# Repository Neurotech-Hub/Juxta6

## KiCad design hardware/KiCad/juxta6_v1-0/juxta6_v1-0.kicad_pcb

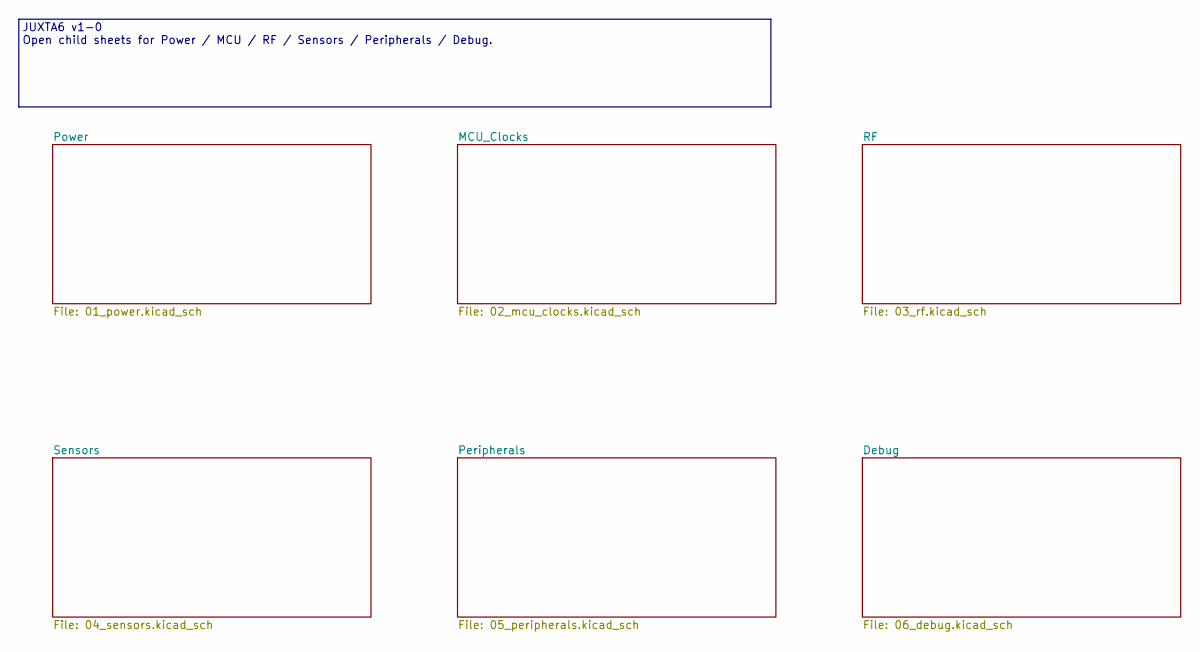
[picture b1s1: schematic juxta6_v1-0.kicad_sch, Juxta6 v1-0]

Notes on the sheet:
JUXTA6 v1-0 Open child sheets for Power / MCU / RF / Sensors / Peripherals / Debug.

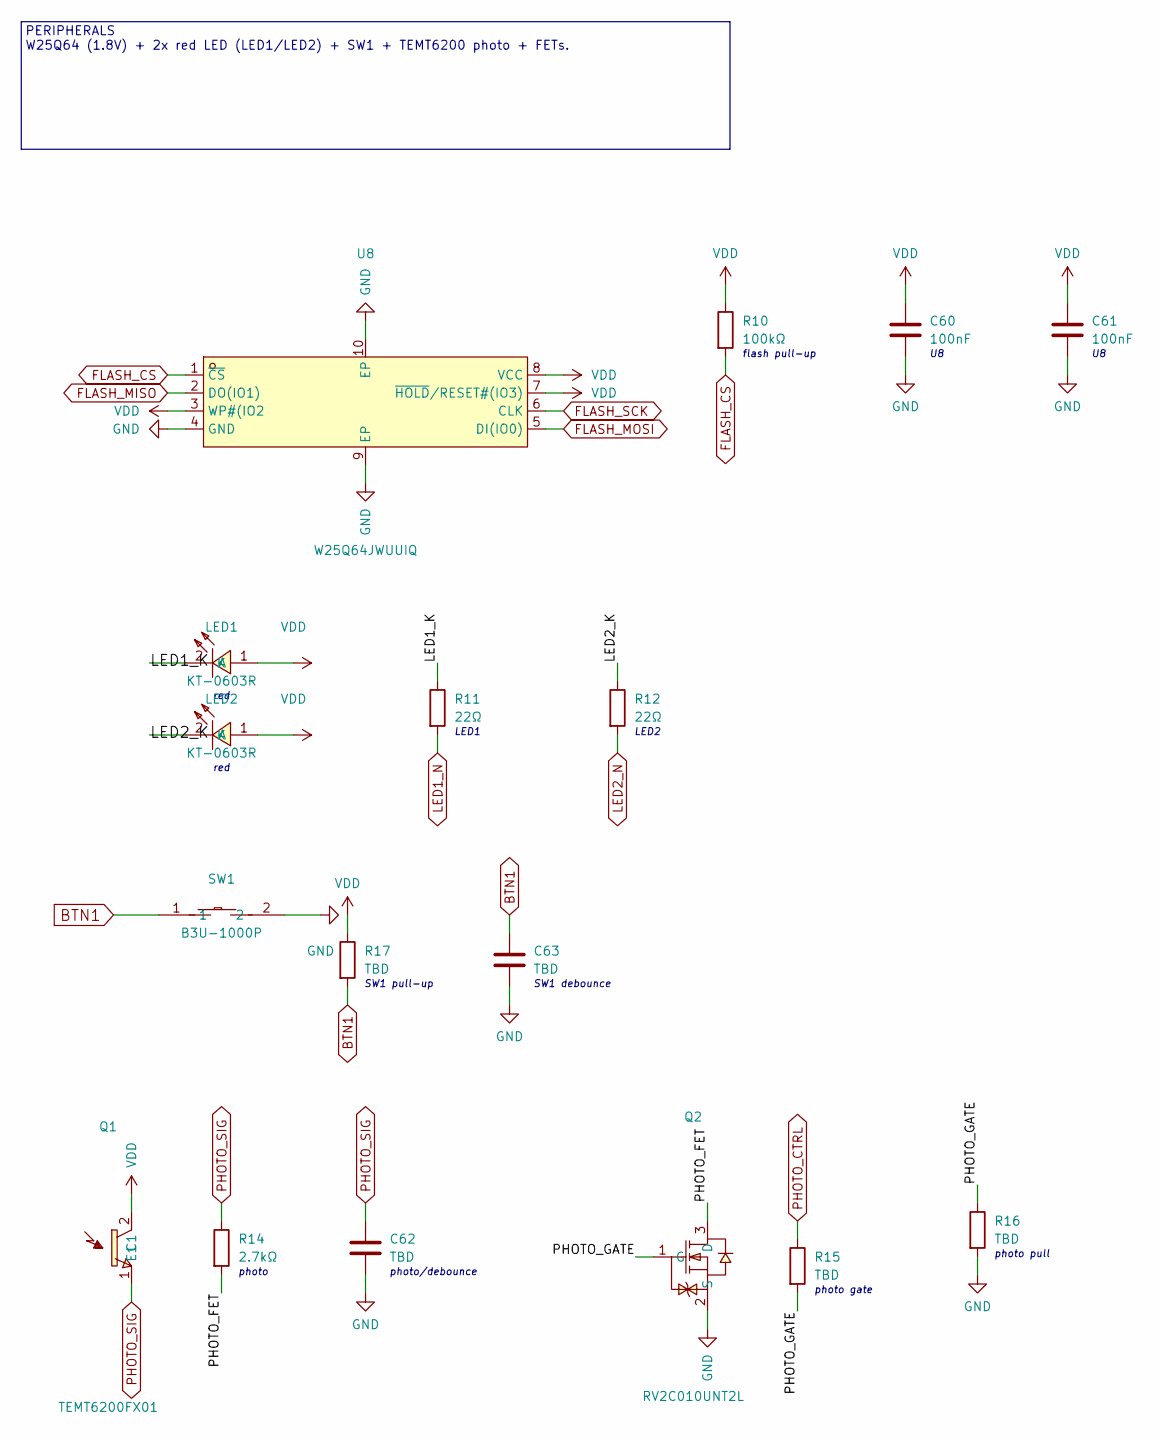
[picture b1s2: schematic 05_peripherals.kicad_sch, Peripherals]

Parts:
C60, C61: 100nF; C_0201_0603Metric
C62, C63: TBD; C_0201_0603Metric
LED1, LED2: KT-0603R; LED-SMD_L1.6-W0.8-R-RD; LCSC C2286
Q1: TEMT6200FX01; SENSORS-SMD_0805; LCSC C143695
Q2: RV2C010UNT2L; X2-DFN1006-3_L1.0-W0.6-BR; LCSC C570828
R10: 100kΩ; R_0201_0603Metric
R11, R12: 22Ω; R_0201_0603Metric
R14: 2.7kΩ; R_0201_0603Metric
R15, R16, R17: TBD; R_0201_0603Metric
SW1: B3U-1000P; KEY-SMD_B3U-1000PM; LCSC C231329
U8: W25Q64JWUUIQ; USON-8_L4.0-W3.0-P0.80-BL_WINBOND_UU; LCSC C6604692

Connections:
/Peripherals/LED1_K: LED1.2 (K), R11.1
/Peripherals/LED2_K: LED2.2 (K), R12.1
/Peripherals/PHOTO_FET: Q2.3 (D), R14.2
/Peripherals/PHOTO_GATE: Q2.1 (G), R15.2, R16.1
BTN1: C63.1, R17.2, SW1.1; also elsewhere on the board
FLASH_CS: R10.2, U8.1 (~CS); also elsewhere on the board
FLASH_MISO: U8.2 (DO(IO1)); also elsewhere on the board
FLASH_MOSI: U8.5 (DI(IO0)); also elsewhere on the board
FLASH_SCK: U8.6 (CLK); also elsewhere on the board
GND: C60.2, C61.2, C62.2, C63.2, Q2.2 (S), R16.2, SW1.2, U8.4 (GND), U8.9 (EP), U8.10 (EP); also elsewhere on the board
LED1_N: R11.2; also elsewhere on the board
LED2_N: R12.2; also elsewhere on the board
PHOTO_CTRL: R15.1; also elsewhere on the board
PHOTO_SIG: C62.1, Q1.1 (E1), R14.1; also elsewhere on the board
VDD: C60.1, C61.1, LED1.1 (A), LED2.1 (A), Q1.2 (C1), R10.1, R17.1, U8.3 (WP#(IO2), U8.7 (~HOLD/RESET#(IO3)), U8.8 (VCC); also elsewhere on the board

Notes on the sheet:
red
LED2
photo gate
photo
flash pull-up
SW1 debounce
LED1
photo pull
SW1 pull-up
photo/debounce
PERIPHERALS W25Q64 (1.8V) + 2x red LED (LED1/LED2) + SW1 + TEMT6200 photo + FETs.

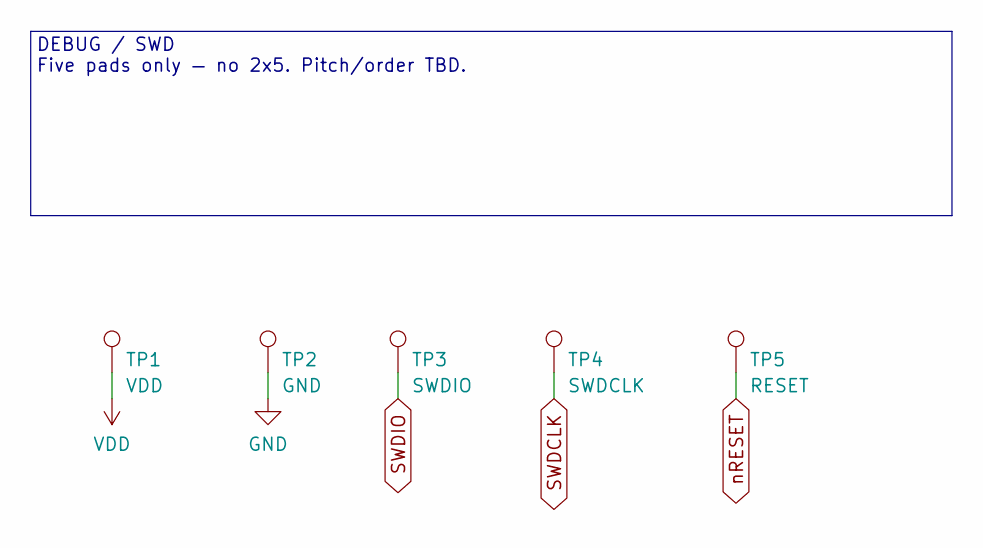
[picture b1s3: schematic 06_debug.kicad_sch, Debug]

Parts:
TP1: VDD; TestPoint_Pad_D1.5mm
TP2: GND; TestPoint_Pad_D1.5mm
TP3: SWDIO; TestPoint_Pad_D1.5mm
TP4: SWDCLK; TestPoint_Pad_D1.5mm
TP5: RESET; TestPoint_Pad_D1.5mm

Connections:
GND: TP2.1 (1_1); also elsewhere on the board
SWDCLK: TP4.1 (1_1); also elsewhere on the board
SWDIO: TP3.1 (1_1); also elsewhere on the board
VDD: TP1.1 (1_1); also elsewhere on the board
nRESET: TP5.1 (1_1); also elsewhere on the board

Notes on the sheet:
DEBUG / SWD Five pads only — no 2x5. Pitch/order TBD.

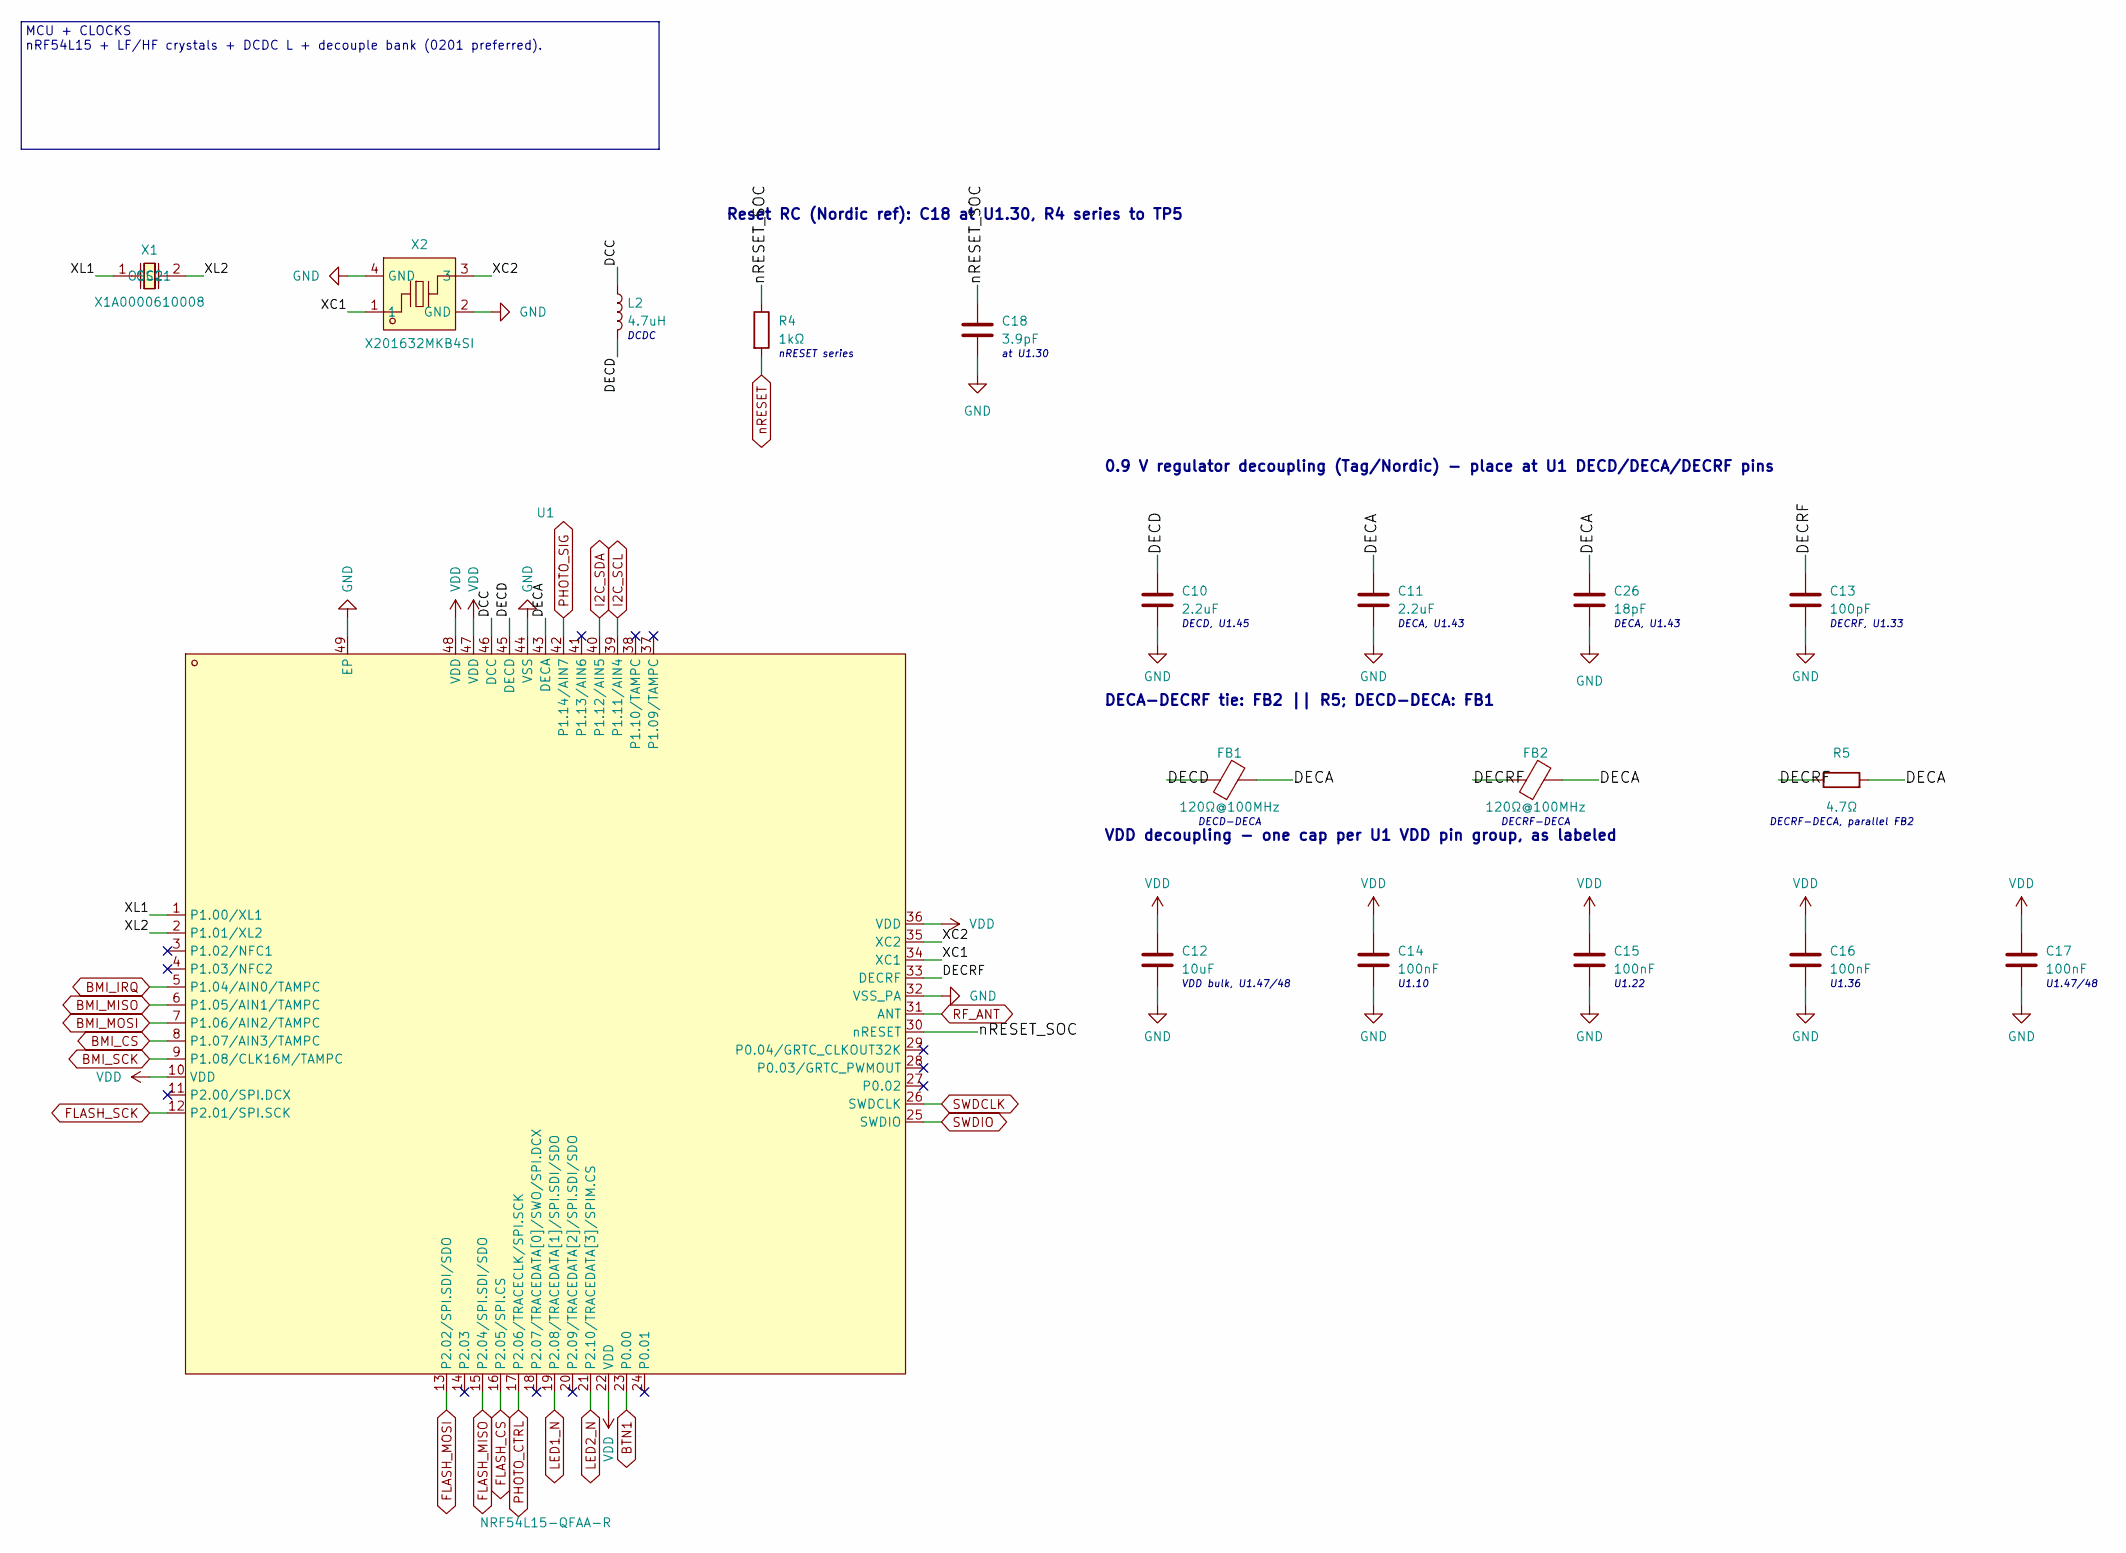
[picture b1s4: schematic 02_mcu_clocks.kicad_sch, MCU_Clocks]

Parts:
C10, C11: 2.2uF; C_0201_0603Metric
C12: 10uF; C_0201_0603Metric
C13: 100pF; C_0201_0603Metric
C14, C15, C16, C17: 100nF; C_0201_0603Metric
C18: 3.9pF; C_0201_0603Metric
C26: 18pF; C_0201_0603Metric
FB1, FB2: 120Ω@100MHz; L_0201_0603Metric
L2: 4.7uH; L_0603_1608Metric
R4: 1kΩ; R_0201_0603Metric
R5: 4.7Ω; R_0201_0603Metric
U1: NRF54L15-QFAA-R; QFN-48_L6.0-W6.0-P0.40-TL-EP4.6; LCSC C42458750
X1: X1A0000610008; OSC-SMD_L2.0-W1.2; LCSC C96341
X2: X201632MKB4SI; CRYSTAL-SMD_4P-L2.0-W1.6-BL; LCSC C718072

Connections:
/MCU_Clocks/DCC: L2.1, U1.46 (DCC)
/MCU_Clocks/DECA: C11.1, C26.1, FB1.2, FB2.2, R5.2, U1.43 (DECA)
/MCU_Clocks/DECD: C10.1, FB1.1, L2.2, U1.45 (DECD)
/MCU_Clocks/DECRF: C13.1, FB2.1, R5.1, U1.33 (DECRF)
/MCU_Clocks/XC1: U1.34 (XC1), X2.1
/MCU_Clocks/XC2: U1.35 (XC2), X2.3
/MCU_Clocks/XL1: U1.1 (P1.00/XL1), X1.1 (OSC1)
/MCU_Clocks/XL2: U1.2 (P1.01/XL2), X1.2 (OSC2)
/MCU_Clocks/nRESET_SOC: C18.1, R4.1, U1.30 (nRESET)
BMI_CS: U1.8 (P1.07/AIN3/TAMPC); also elsewhere on the board
BMI_IRQ: U1.5 (P1.04/AIN0/TAMPC); also elsewhere on the board
BMI_MISO: U1.6 (P1.05/AIN1/TAMPC); also elsewhere on the board
BMI_MOSI: U1.7 (P1.06/AIN2/TAMPC); also elsewhere on the board
BMI_SCK: U1.9 (P1.08/CLK16M/TAMPC); also elsewhere on the board
BTN1: U1.23 (P0.00); also elsewhere on the board
FLASH_CS: U1.16 (P2.05/SPI.CS); also elsewhere on the board
FLASH_MISO: U1.15 (P2.04/SPI.SDI/SDO); also elsewhere on the board
FLASH_MOSI: U1.13 (P2.02/SPI.SDI/SDO); also elsewhere on the board
FLASH_SCK: U1.12 (P2.01/SPI.SCK); also elsewhere on the board
GND: C10.2, C11.2, C12.2, C13.2, C14.2, C15.2, C16.2, C17.2, C18.2, C26.2, U1.32 (VSS_PA), U1.44 (VSS), U1.49 (EP), X2.2 (GND), X2.4 (GND); also elsewhere on the board
I2C_SCL: U1.39 (P1.11/AIN4); also elsewhere on the board
I2C_SDA: U1.40 (P1.12/AIN5); also elsewhere on the board
LED1_N: U1.19 (P2.08/TRACEDATA[1]/SPI.SDI/SDO); also elsewhere on the board
LED2_N: U1.21 (P2.10/TRACEDATA[3]/SPIM.CS); also elsewhere on the board
PHOTO_CTRL: U1.17 (P2.06/TRACECLK/SPI.SCK); also elsewhere on the board
PHOTO_SIG: U1.42 (P1.14/AIN7); also elsewhere on the board
RF_ANT: U1.31 (ANT); also elsewhere on the board
SWDCLK: U1.26 (SWDCLK); also elsewhere on the board
SWDIO: U1.25 (SWDIO); also elsewhere on the board
VDD: C12.1, C14.1, C15.1, C16.1, C17.1, U1.10 (VDD), U1.22 (VDD), U1.36 (VDD), U1.47 (VDD), U1.48 (VDD); also elsewhere on the board
nRESET: R4.2; also elsewhere on the board

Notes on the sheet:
U1.10
DCDC
DECA, U1.43
DECD, U1.45
0.9 V regulator decoupling (Tag/Nordic) - place at U1 DECD/DECA/DECRF pins
VDD bulk, U1.47/48
VDD decoupling - one cap per U1 VDD pin group, as labeled
nRESET series
at U1.30
DECRF, U1.33
U1.47/48
U1.22
Reset RC (Nordic ref): C18 at U1.30, R4 series to TP5
DECD-DECA
DECRF-DECA, parallel FB2
U1.36
DECRF-DECA
DECA-DECRF tie: FB2 || R5; DECD-DECA: FB1
MCU + CLOCKS nRF54L15 + LF/HF crystals + DCDC L + decouple bank (0201 preferred).

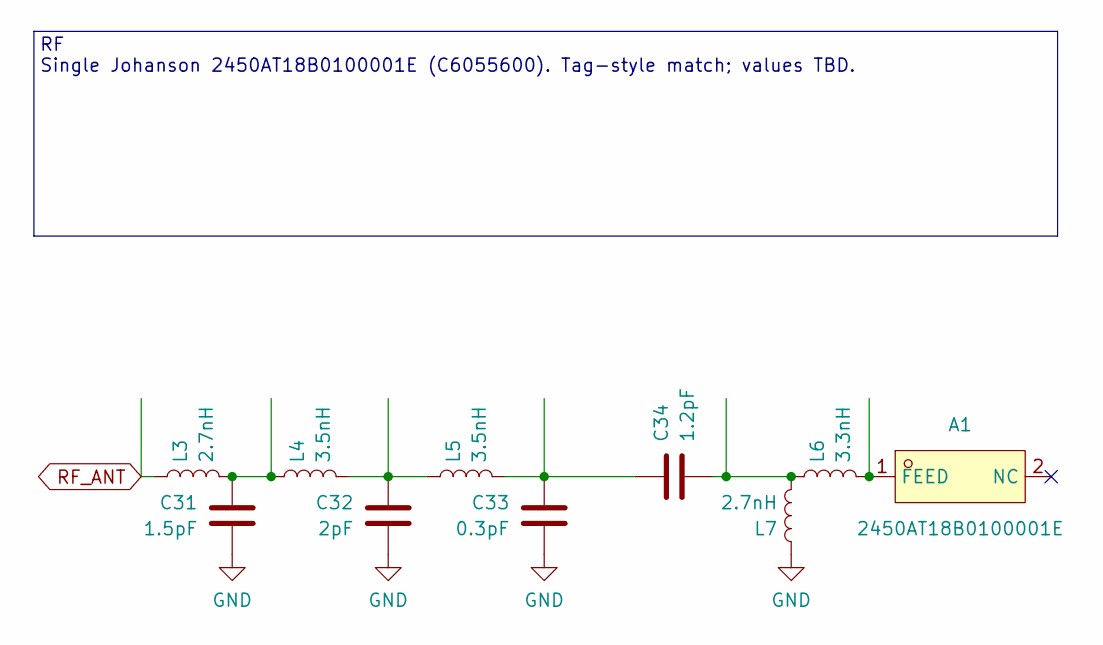
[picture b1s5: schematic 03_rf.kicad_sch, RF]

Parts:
A1: 2450AT18B0100001E; ANT-SMD_L3.2-W1.6
C31: 1.5pF; C_0201_0603Metric
C32: 2pF; C_0201_0603Metric
C33: 0.3pF; C_0201_0603Metric
C34: 1.2pF; C_0201_0603Metric
L3, L7: 2.7nH; L_0201_0603Metric
L4, L5: 3.5nH; L_0201_0603Metric
L6: 3.3nH; L_0201_0603Metric

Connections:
GND: C31.2, C32.2, C33.2, L7.1; also elsewhere on the board
unnamed: A1.1 (FEED_1), L6.2
unnamed: C31.1, L3.2, L4.1
unnamed: C32.1, L4.2, L5.1
unnamed: C33.1, C34.1, L5.2
unnamed: C34.2, L6.1, L7.2
RF_ANT: L3.1; also elsewhere on the board

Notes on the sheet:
RF Single Johanson 2450AT18B0100001E (C6055600). Tag-style match; values TBD.

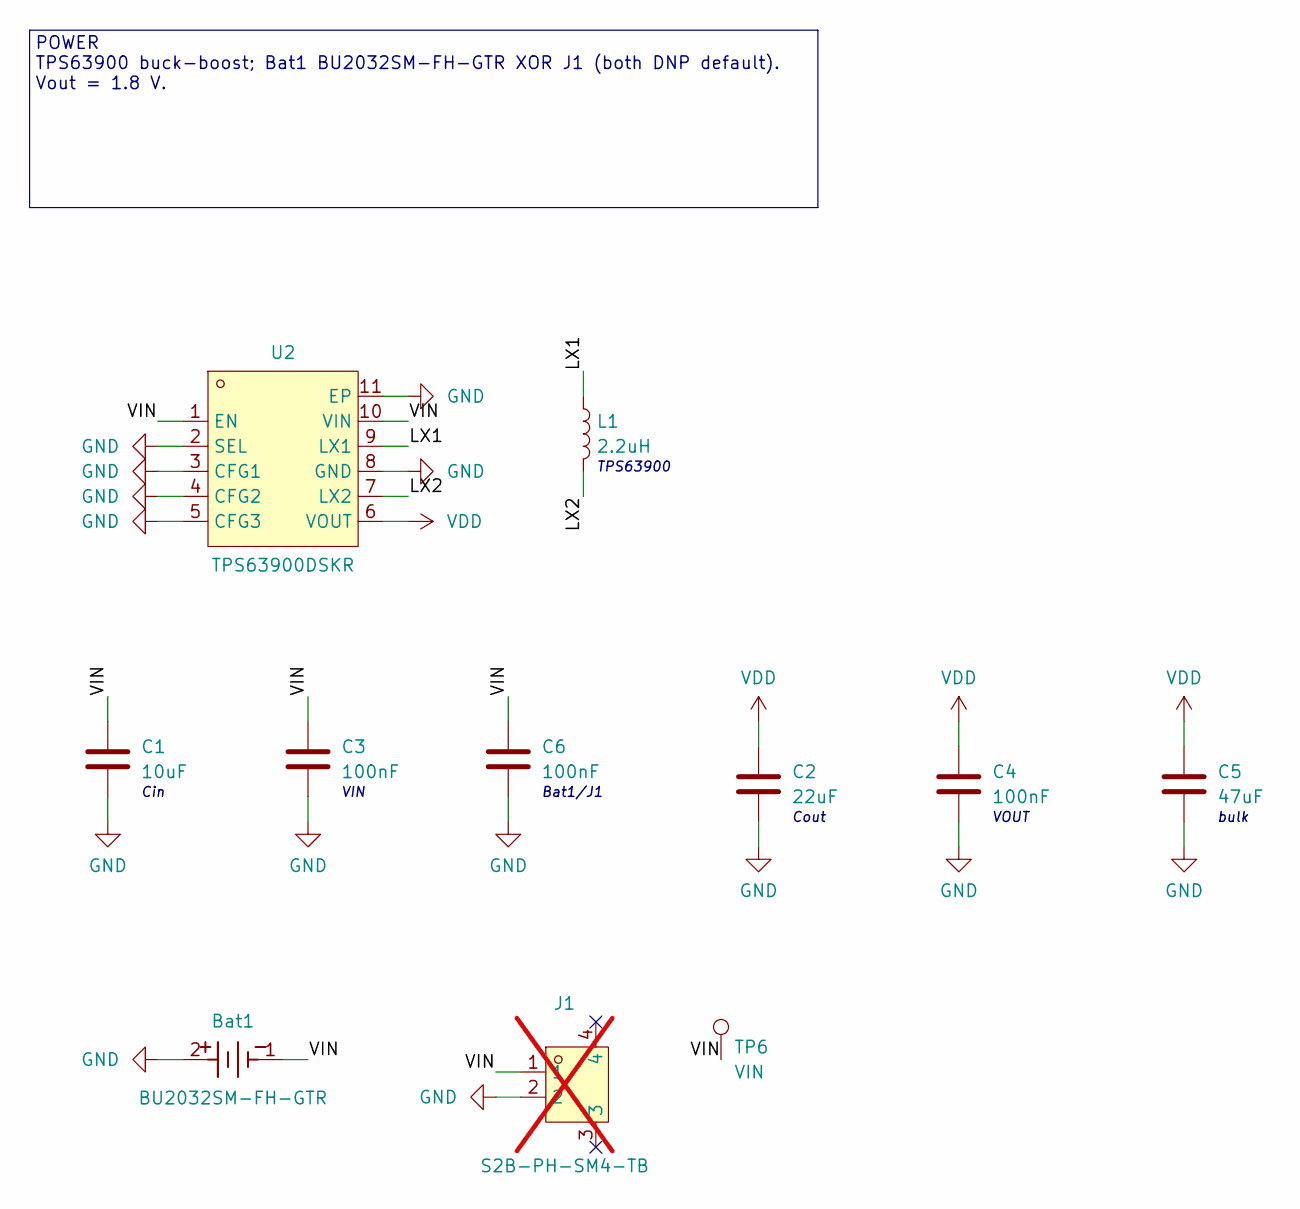
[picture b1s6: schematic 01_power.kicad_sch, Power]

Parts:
Bat1: BU2032SM-FH-GTR; BU2032SM-FH-GTR_MPD; LCSC C6755625
C1: 10uF; C_0603_1608Metric
C2: 22uF; C_0603_1608Metric
C3, C4, C6: 100nF; C_0201_0603Metric
C5: 47uF; C_0603_1608Metric
J1: S2B-PH-SM4-TB; CONN-SMD_P2.00_S2B-PH-SM4-TB-LF-SN; LCSC C295747; not fitted
L1: 2.2uH; L_0805_2012Metric
TP6: VIN; TestPoint_Pad_D1.5mm
U2: TPS63900DSKR; WSON-10_L2.5-W2.5-W0.50-TL-EP; LCSC C1518762

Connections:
/Power/LX1: L1.1, U2.9 (LX1)
/Power/LX2: L1.2, U2.7 (LX2)
/Power/VIN: Bat1.1, C1.1, C3.1, C6.1, J1.1, TP6.1 (1_1), U2.1 (EN), U2.10 (VIN)
GND: Bat1.2, C1.2, C2.2, C3.2, C4.2, C5.2, C6.2, J1.2, U2.2 (SEL), U2.3 (CFG1), U2.4 (CFG2), U2.5 (CFG3), U2.8 (GND), U2.11 (EP); also elsewhere on the board
VDD: C2.1, C4.1, C5.1, U2.6 (VOUT); also elsewhere on the board

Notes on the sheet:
Cin
bulk
TPS63900
VOUT
Bat1/J1
VIN
Cout
POWER TPS63900 buck-boost; Bat1 BU2032SM-FH-GTR XOR J1 (both DNP default). Vout = 1.8 V.

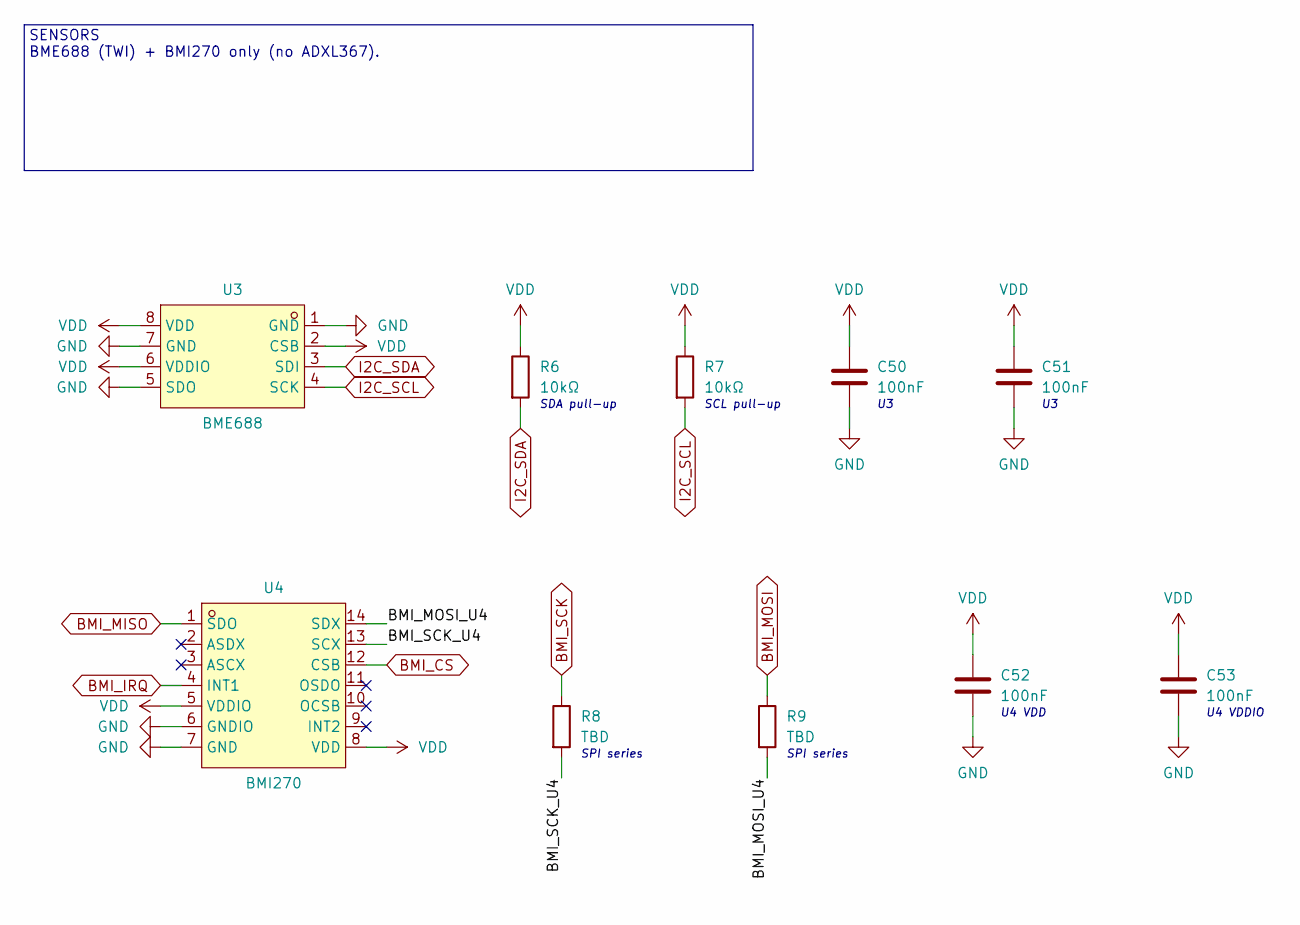
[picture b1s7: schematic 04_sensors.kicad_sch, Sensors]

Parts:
C50, C51, C52, C53: 100nF; C_0201_0603Metric
R6, R7: 10kΩ; R_0201_0603Metric
R8, R9: TBD; R_0201_0603Metric
U3: BME688; LGA-8_L3.0-W3.0-P0.80_BME688; LCSC C3664478
U4: BMI270; LGA-14_L3.0-W2.5-P0.50-BR; LCSC C2836813

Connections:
/Sensors/BMI_MOSI_U4: R9.2, U4.14 (SDX)
/Sensors/BMI_SCK_U4: R8.2, U4.13 (SCX)
BMI_CS: U4.12 (CSB); also elsewhere on the board
BMI_IRQ: U4.4 (INT1); also elsewhere on the board
BMI_MISO: U4.1 (SDO); also elsewhere on the board
BMI_MOSI: R9.1; also elsewhere on the board
BMI_SCK: R8.1; also elsewhere on the board
GND: C50.2, C51.2, C52.2, C53.2, U3.1 (GND), U3.5 (SDO), U3.7 (GND), U4.6 (GNDIO), U4.7 (GND); also elsewhere on the board
I2C_SCL: R7.2, U3.4 (SCK); also elsewhere on the board
I2C_SDA: R6.2, U3.3 (SDI); also elsewhere on the board
VDD: C50.1, C51.1, C52.1, C53.1, R6.1, R7.1, U3.2 (CSB), U3.6 (VDDIO), U3.8 (VDD), U4.5 (VDDIO), U4.8 (VDD); also elsewhere on the board

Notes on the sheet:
U4 VDDIO
SDA pull-up
SPI series
U4 VDD
SCL pull-up
SENSORS BME688 (TWI) + BMI270 only (no ADXL367).

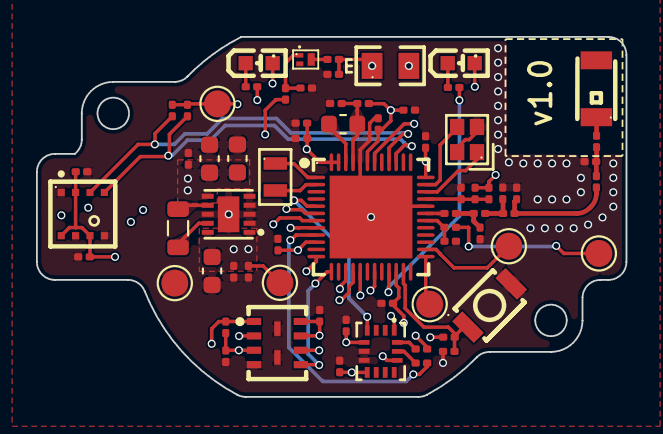
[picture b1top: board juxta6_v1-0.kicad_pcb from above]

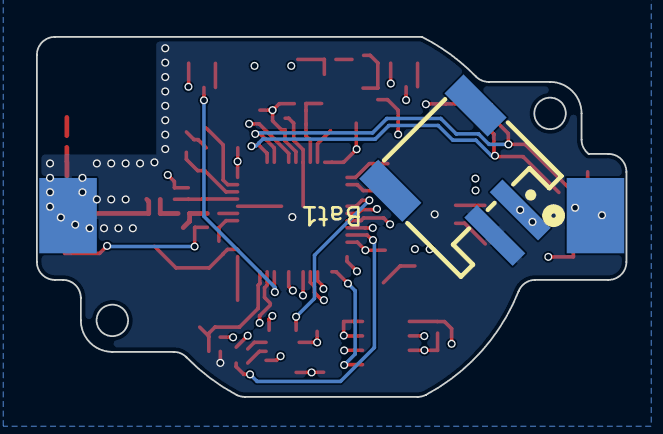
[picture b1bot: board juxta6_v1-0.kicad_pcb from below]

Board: 4 copper layers, 32.8 x 20.0 mm, 71 parts (2 on the bottom side), 45 nets.
